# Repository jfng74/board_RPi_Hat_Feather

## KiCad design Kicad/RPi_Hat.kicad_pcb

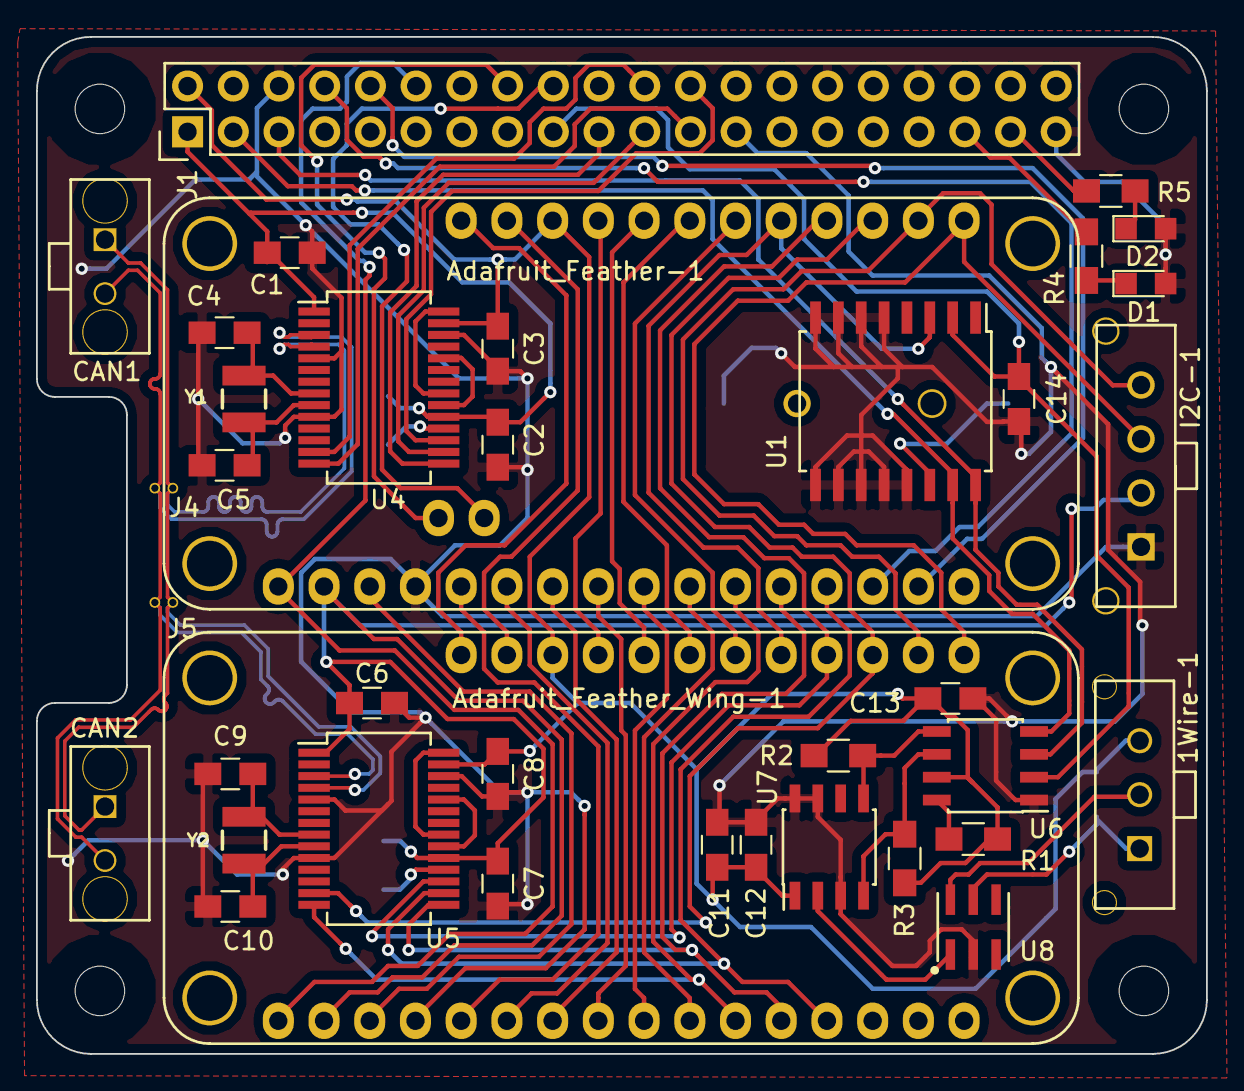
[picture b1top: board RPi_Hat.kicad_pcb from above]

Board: 2 copper layers, 65.0 x 56.5 mm, 43 parts (0 on the bottom side), 60 nets.

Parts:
1Wire-1: CONN_01X03; 0436500317
Adafruit_Feather-1: FEATHER_MO_LORA
Adafruit_Feather_Wing-1: FEATHER_WING
BT1: Battery_Cell; BC501SM
C1, C2, C3, C6, C7, C8, C13, C14, C15: 0.1u; C_0805_HandSoldering
C4, C5, C9, C10: 10pF; C_0805_HandSoldering
C11: 1uf; C_0805_HandSoldering
C12: 0.1uf; C_0805_HandSoldering
C16: 1uF; C_0805_HandSoldering
CAN1, CAN2: CONN_01X02; 0436500219
D1, D2: LED; LED_0805
I2C-1: CONN_01X04; 0436500417
J1: RPi_GPIO; Pin_Header_Straight_2x20
J4, J5: CAN_NODE_JUNCTION; CAN_NODE_JONCTION
R1: 200k; R_0805_HandSoldering
R2, R3: 4.7k; R_0805_HandSoldering
R4, R5: 1k; R_0805_HandSoldering
R6, R7: 10k; R_0805_HandSoldering
U1: DS3231; SOIC-16W_7.5x10.3mm_Pitch1.27mm
U4, U5: MCP25625; SSOP-28_5.3x10.2mm_Pitch0.65mm
U6: PCA9306; SOIC-8_3.9x4.9mm_Pitch1.27mm
U7: DS2482-100; SOIC-8_3.9x4.9mm_Pitch1.27mm
U8: DS9503; TSOC-6
Y1, Y2: 16MHz; SMD-2520

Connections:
+3V3: C1.1, C2.1, C14.1, J1.1, J1.17, R6.1, U1.2, U4.1, U4.19, U6.2
+5V: 1Wire-1.3, Adafruit_Feather-1.29, Adafruit_Feather_Wing-1.29, C3.2, C8.2, C11.1, C12.1, C13.2, C16.2, J1.2, J1.4, R1.2, R2.2, R3.2, U4.27, U5.27, U6.7, U7.1
/1-wire/1_WIRE_GND: 1Wire-1.1, C16.1, U8.5
/1-wire/1_WIRE_IO: 1Wire-1.2, U8.6
/1-wire/1_wire: U7.2, U8.1
/1-wire/_scl: R3.1, U6.6, U7.4
/1-wire/_sda: R2.1, U6.5, U7.5
/CAN+: CAN1.1, CAN2.1, J4.1, J5.1, U4.4, U5.4
/CAN-: CAN1.2, CAN2.2, J4.2, J5.2, U4.3, U5.3
/RPi_GPIO/MCP2515_CS_SPI: J1.24, U4.17
/RPi_GPIO/MCP2515_INT: J1.22, U4.13
/RPi_GPIO/RPi_CLK_SPI: J1.23, U4.14
/RPi_GPIO/RPi_MISO_SPI: J1.21, U4.16
/RPi_GPIO/RPi_MOSI_SPI: J1.19, U4.15
/RPi_GPIO/RPi_SCL_I2C: J1.5, U1.16, U6.3
/RPi_GPIO/RPi_SDA_I2C: J1.3, U1.15, U6.4
/RPi_GPIO/nRST: Adafruit_Feather-1.16, Adafruit_Feather_Wing-1.16, J1.12
/RPi_GPIO/swclk: Adafruit_Feather-1.33, J1.16
/RPi_GPIO/swdio: Adafruit_Feather-1.32, J1.18
/RTC/INT_SQW: Adafruit_Feather-1.24, Adafruit_Feather_Wing-1.24, U1.3
/RTC/VBAT: BT1.1, U1.14
/feather_connectors/A0: Adafruit_Feather-1.12, Adafruit_Feather_Wing-1.12
/feather_connectors/A1: Adafruit_Feather-1.11, Adafruit_Feather_Wing-1.11
/feather_connectors/A2: Adafruit_Feather-1.10, Adafruit_Feather_Wing-1.10
/feather_connectors/A3: Adafruit_Feather-1.9, Adafruit_Feather_Wing-1.9
/feather_connectors/A4: Adafruit_Feather-1.8, Adafruit_Feather_Wing-1.8
/feather_connectors/A5: Adafruit_Feather-1.7, Adafruit_Feather_Wing-1.7
/feather_connectors/ARF: Adafruit_Feather-1.14, Adafruit_Feather_Wing-1.14
/feather_connectors/D10: Adafruit_Feather-1.25, Adafruit_Feather_Wing-1.25
/feather_connectors/D11: Adafruit_Feather-1.26, Adafruit_Feather_Wing-1.26
/feather_connectors/D12: Adafruit_Feather-1.27, Adafruit_Feather_Wing-1.27
/feather_connectors/D13: Adafruit_Feather-1.28, Adafruit_Feather_Wing-1.28
/feather_connectors/EN: Adafruit_Feather-1.30, Adafruit_Feather_Wing-1.30
/feather_connectors/FEATHER_3.3V: Adafruit_Feather-1.15, Adafruit_Feather_Wing-1.15, C6.1, C7.1, C15.2, I2C-1.2, R7.1, U5.1, U5.19
/feather_connectors/FEATHER_MISO_SPI: Adafruit_Feather-1.4, Adafruit_Feather_Wing-1.4, U5.16
/feather_connectors/FEATHER_MOSI_SPI: Adafruit_Feather-1.5, Adafruit_Feather_Wing-1.5, U5.15
/feather_connectors/FEATHER_RXD: Adafruit_Feather-1.3, J1.8
/feather_connectors/FEATHER_SCK_SPI: Adafruit_Feather-1.6, Adafruit_Feather_Wing-1.6, U5.14
/feather_connectors/FEATHER_SCL_I2C: Adafruit_Feather-1.21, Adafruit_Feather_Wing-1.21, I2C-1.4
/feather_connectors/FEATHER_SDA_I2C: Adafruit_Feather-1.20, Adafruit_Feather_Wing-1.20, I2C-1.3
/feather_connectors/FEATHER_TXD: Adafruit_Feather-1.2, J1.10
/feather_connectors/MCP2515_CS: Adafruit_Feather-1.23, Adafruit_Feather_Wing-1.23, U5.17
/feather_connectors/MCP2515_INT: Adafruit_Feather-1.22, Adafruit_Feather_Wing-1.22, U5.13
/feather_connectors/VBAT: Adafruit_Feather-1.31, Adafruit_Feather_Wing-1.31
GND: Adafruit_Feather-1.13, Adafruit_Feather_Wing-1.13, BT1.2, C1.2, C2.2, C3.1, C4.1, C5.1, C6.2, C7.2, C8.1, C9.1, C10.1, C11.2, C12.2, C13.1, C14.2, C15.1, D1.2, D2.2, I2C-1.1, J1.6, J1.9, J1.14, J1.20, J1.25, J1.30, J1.34, J1.39, U1.5, U1.6, U1.7, U1.8, U1.9, U1.10, U1.11, U1.12, U1.13, U4.5, U4.10, U4.26, U5.5, U5.10, U5.26, U6.1, U7.3, U7.7, U7.8, U8.2
unnamed: C4.2, U4.8, Y1.1
unnamed: C5.2, U4.9, Y1.2
unnamed: C9.2, U5.8, Y2.1
unnamed: C10.2, U5.9, Y2.2
unnamed: D1.1, R4.2
unnamed: D2.1, R5.2
unnamed: J1.35, R4.1
unnamed: J1.37, R5.1
unnamed: R1.1, U6.8
unnamed: R6.2, U4.18
unnamed: R7.2, U5.18
unnamed: U4.20, U4.24
unnamed: U4.21, U4.28
unnamed: U5.20, U5.24
unnamed: U5.21, U5.28

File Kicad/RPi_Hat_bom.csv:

Component,Description,Part,References,Value,Footprint,Quantity Per PCB,Datasheet,Mouser Part No.,Digikey Part Number,Manufacturer Part Number
1,"Connector, single row, 01x03, pin header",CONN_01X03,1Wire-1,CONN_01X03,0436500317,1,,,,
2,,FEATHER_MO_LORA-RESCUE-pihat_template,Adafruit_Feather-1,FEATHER_MO_LORA,FEATHER_MO_LORA,1,,,,
3,,FEATHER_WING,Adafruit_Feather_Wing-1,FEATHER_WING,FEATHER_WING,1,,,,
4,single battery cell,Battery_Cell,BT1,Battery_Cell,BC501SM,1,,,,
5,Unpolarized capacitor,C_Small,C1 C2 C3 C6 C7 C8 C12 C13 C14 C15,0.1u,C_0805_HandSoldering,10,,810-C1005X5R1H104K,,
6,Unpolarized capacitor,C_Small,C4 C5 C9 C10,10pF,C_0805_HandSoldering,4,,,,
7,Unpolarized capacitor,C,C11,1uf,C_0805_HandSoldering,1,,810-C1005X5R1H104K,,
8,"Connector, single row, 01x02, pin header",CONN_01X02,CAN1 CAN2,CONN_01X02,0436500219,2,,,,
9,LED generic,LED,D1 D2,LED,LED_0805,2,,,,
10,"Connector, single row, 01x04, pin header",CONN_01X04,I2C-1,CONN_01X04,0436500417,1,,,,
11,"Connector, single row, 01x02",CAN_NODE_JUNCTION,J4 J5,CAN_NODE_JUNCTION,CAN_NODE_JONCTION,2,,,,
12,,RPi_GPIO,J1,RPi_GPIO,Pin_Header_Straight_2x20,1,,,,
13,Resistor,R,R4 R5,1k,R_0805_HandSoldering,2,,,,
14,Resistor,R,R1,200k,R_0805_HandSoldering,1,,,,
15,Resistor,R,R2 R3,4.7k,R_0805_HandSoldering,2,,,,
16,,DS2482-100,U7,DS2482-100,SOIC-8_3.9x4.9mm_Pitch1.27mm,1,,,,
17,Extremely Accurate I2C-Integrated RTC/TCXO/Crystal SOIC-16,DS3231,U1,DS3231,SOIC-16W_7.5x10.3mm_Pitch1.27mm,1,http://datasheets.maximintegrated.com/en/ds/DS3231.pdf,,,
18,,DS9503,U8,DS9503,TSOC-6,1,,,DS9503P+T&RCT-ND,DS9503P+T&R
19,,MCP25625,U4 U5,MCP25625,SSOP-28_5.3x10.2mm_Pitch0.65mm,2,,,,
20,,PCA9306-RESCUE-RPi_Hat,U6,PCA9306,SOIC-8_3.9x4.9mm_Pitch1.27mm,1,,,568-4215-1-ND,"PCA9306D,118"
21,"Two pin crystal, small symbol",Crystal_Small,Y1 Y2,16MHz,SMD-2520,2,,,,





Component Groups:,21
Component Count:,40
Fitted Components:,40
Number of PCBs:,1
Total components:,40
Schematic Version:,
Schematic Date:,2017-02-08
BoM Date:,lun 08 mai 2017 16:11:01 EDT
Schematic Source:,/home/caribou/git_rep/board_RPi_Hat_Feather/Kicad/RPi_Hat.sch
KiCad Version:,Eeschema no-vcs-found-01f5a12~58~ubuntu16.04.1

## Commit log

2017-05-16 Ajout du repertoire Applications
2017-05-16 Ajout du repertoire Kicad
2017-07-06 Mise a jour du 6 juillet 2017
2017-07-19 modification de platform.ini
2018-01-28 Reouverture avec une nouvelle version de Kicad
2018-01-28 Modification du fichier platformio.ini
2018-04-17 Ajout de test
